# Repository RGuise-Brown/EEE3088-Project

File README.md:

# EEE3088-Project
This repository is used for the collaborative project to create a micromouse with the focus on creating a power and sensing unit which will work with an existing structure, motherboard and processor.This project is being completed by Rachael Guise-Brown and Heinrich Crous for EEE3088F at UCT.

Project Overview:

The project involves building subassemblies for a micro-mouse robot designed to navigate a maze within a set time limit. This repository focuses on the design and fabrication of the following modules:

Power Module: This module will be responsible for powering the motors, charging the battery, switching the robot on and off and providing an indication of the battery level to the processor.
Sensor Module: This module  will be responsible for detecting objects in the maze environment and relaying this information to the processor for navigation purposes.

Folder Structure:
power_module: This folder will contain all schematics, PCB design files, component selection information, and testing procedures related to the power module.
sensor_module: This folder will contain all design files, documentation, and testing procedures related to the sensor module.
documentation: This folder will contain any information documents linked to both power and sensor modules.

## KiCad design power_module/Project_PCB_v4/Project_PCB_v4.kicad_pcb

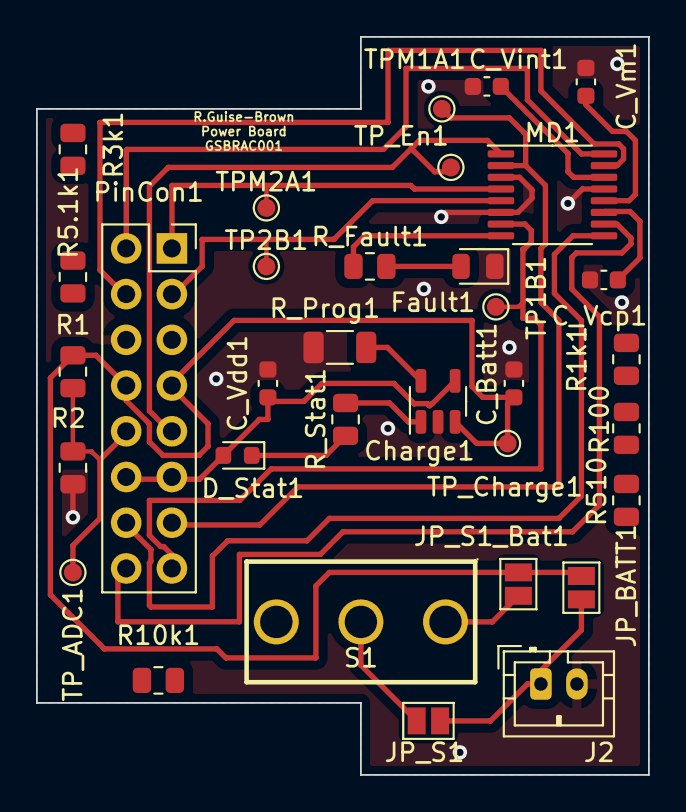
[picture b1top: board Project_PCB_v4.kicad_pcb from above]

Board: 2 copper layers, 34.0 x 41.0 mm, 33 parts (0 on the bottom side), 24 nets.

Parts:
C_Batt1: 4.7uF; C_0603_1608Metric
C_Vcp1: 10nF; C_0603_1608Metric
C_Vdd1: 4.7uF; C_0603_1608Metric
C_Vint1: 2.2uF; C_0603_1608Metric
C_Vm1: 10uF; C_0603_1608Metric
Charge1: MCP73831-2-OT; SOT-23-5
D_Stat1: LED_Red; LED_0603_1608Metric
Fault1: LED_Green; LED_0805_2012Metric
J2: Conn_01x02; JST_PH_B2B-PH-K_1x02_P2.00mm_Vertical
JP_BATT1: Jumper_2_Open; SolderJumper-2_P1.3mm_Open_Pad1.0x1.5mm
JP_S1, JP_S1_Bat1: Jumper_2_Open; SolderJumper-2_P1.3mm_Open_Pad1.0x1.5mm
MD1: DRV8833PW; TSSOP-16_4.4x5mm_P0.65mm
PinCon1: Conn_02x08_Odd_Even; PinSocket_2x08_P2.54mm_Vertical
R1: 1.2kR; R_0805_2012Metric
R1k1: 1k; R_0805_2012Metric
R2: 3.0kR; R_0805_2012Metric
R3k1: 3k; R_0805_2012Metric
R5.1k1: 5.1k; R_0805_2012Metric
R10k1: 10k; R_0805_2012Metric
R100: 100R; R_0805_2012Metric
R510: 510; R_0805_2012Metric
R_Fault1: 100R; R_0805_2012Metric
R_Prog1: 2k; R_1206_3216Metric
R_Stat1: 470R; R_0805_2012Metric
S1: SS-12D10L5; SW-TH_SS-12D10L5
TP1B1, TP2B1: TestPoint; TestPoint_Pad_D1.0mm
TPM1A1, TPM2A1: TestPoint; TestPoint_Pad_D1.0mm
TP_ADC1: TestPoint; TestPoint_Pad_D1.0mm
TP_Charge1: TestPoint; TestPoint_Pad_D1.0mm
TP_En1: TestPoint; TestPoint_Pad_D1.0mm

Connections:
5V_1: C_Vdd1.1, Charge1.4 (VDD), D_Stat1.2 (A), PinCon1.11, PinCon1.12
BATT_1: C_Batt1.1, Charge1.3 (VBAT), JP_BATT1.2 (B), JP_S1_Bat1.1 (A), PinCon1.7, PinCon1.8, R1.1, TP_Charge1.1
BATT_ADC: PinCon1.10, R1.2, R2.2, TP_ADC1.1
GND: C_Batt1.2, C_Vcp1.1, C_Vdd1.2, C_Vint1.1, C_Vm1.2, Charge1.2 (VSS), Fault1.1 (K), J2.2, MD1.3 (AISEN), MD1.6 (BISEN), MD1.13 (GND), PinCon1.5, PinCon1.6, R2.1, R_Prog1.2
Motor1_A: MD1.2 (AOUT1), PinCon1.13, TPM1A1.1
Motor1_B: MD1.7 (BOUT1), PinCon1.15, TP1B1.1
Motor2_A: MD1.4 (AOUT2), PinCon1.1, TPM2A1.1
Motor2_B: MD1.5 (BOUT2), PinCon1.3, TP2B1.1
unnamed: C_Vcp1.2, MD1.11 (VCP)
unnamed: C_Vint1.2, MD1.14 (VINT)
unnamed: Charge1.1 (STAT), R_Stat1.2
unnamed: Charge1.5 (PROG), R_Prog1.1
unnamed: D_Stat1.1 (K), R_Stat1.1
unnamed: Fault1.2 (A), R_Fault1.2
unnamed: J2.1, JP_BATT1.1 (A), JP_S1.1 (A)
unnamed: JP_S1.2 (B), S1.2
unnamed: JP_S1_Bat1.2 (B), S1.1
unnamed: MD1.8 (nFAULT), R_Fault1.1
PC6-9 PWM1: MD1.16 (AIN1), PinCon1.2
PC6-9 PWM2: MD1.15 (AIN2), PinCon1.4
PC6-9 PWM3: MD1.9 (BIN1), PinCon1.14
PC6-9 PWM4: MD1.10 (BIN2), PinCon1.16
Reserve: MD1.1 (nSLEEP), PinCon1.9, TP_En1.1
VM: C_Vm1.1, MD1.12 (VM)

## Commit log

2024-04-17 documentation/
2024-04-17 Create documentaion_README
2024-04-17 Create power_README
2024-04-21 Create test
2024-04-21 Update and rename test to READme
2024-04-21 Rename READme to README
2024-05-17 Create Screenshots
